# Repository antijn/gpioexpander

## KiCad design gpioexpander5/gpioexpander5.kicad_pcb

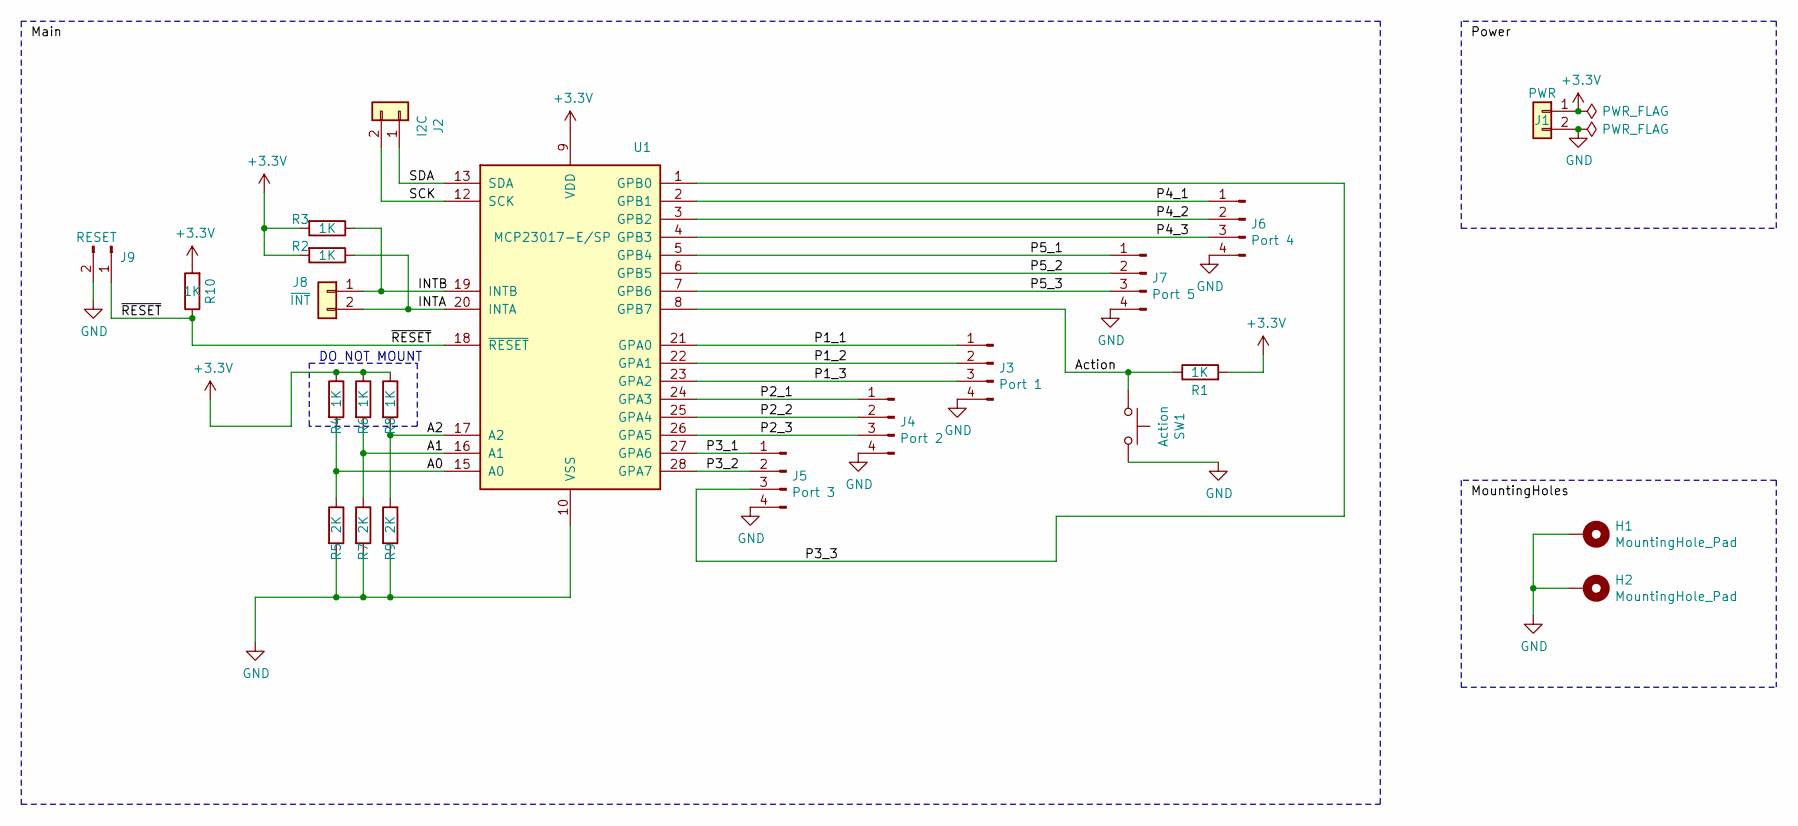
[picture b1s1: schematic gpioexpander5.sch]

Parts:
H1, H2: MountingHole_Pad; MountingHole_3.2mm_M3_Pad
J1: PWR; PinHeader_1x02_P2.54mm_Vertical
J2: I2C; PinHeader_1x02_P2.54mm_Vertical
J3: Port 1; PinHeader_1x04_P2.54mm_Vertical
J4: Port 2; PinHeader_1x04_P2.54mm_Vertical
J5: Port 3; PinHeader_1x04_P2.54mm_Vertical
J6: Port 4; PinHeader_1x04_P2.54mm_Vertical
J7: Port 5; PinHeader_1x04_P2.54mm_Vertical
J8: ~INT; PinHeader_1x02_P2.54mm_Vertical
J9: RESET; PinHeader_1x02_P2.54mm_Vertical
R1, R2, R3, R4, R6, R8, R10: 1K; R_0805_2012Metric_Pad1.15x1.40mm_HandSolder
R5, R7, R9: 2K; R_0805_2012Metric_Pad1.15x1.40mm_HandSolder
SW1: Action; SW_PUSH_6mm
U1: MCP23017-E/SP; SOIC-28W_7.5x17.9mm_P1.27mm

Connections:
+3V3: J1.1, R1.2, R2.2, R3.2, R4.1, R6.1, R8.1, R10.2, U1.9 (VDD)
/A0: R4.2, R5.1, U1.15 (A0)
/A1: R6.2, R7.1, U1.16 (A1)
/A2: R8.2, R9.1, U1.17 (A2)
/Action: R1.1, SW1.1, U1.8 (GPB7)
/INTA: J8.2, R2.1, U1.20 (INTA)
/INTB: J8.1, R3.1, U1.19 (INTB)
/P1_1: J3.1, U1.21 (GPA0)
/P1_2: J3.2, U1.22 (GPA1)
/P1_3: J3.3, U1.23 (GPA2)
/P2_1: J4.1, U1.24 (GPA3)
/P2_2: J4.2, U1.25 (GPA4)
/P2_3: J4.3, U1.26 (GPA5)
/P3_1: J5.1, U1.27 (GPA6)
/P3_2: J5.2, U1.28 (GPA7)
/P3_3: J5.3, U1.1 (GPB0)
/P4_1: J6.1, U1.2 (GPB1)
/P4_2: J6.2, U1.3 (GPB2)
/P4_3: J6.3, U1.4 (GPB3)
/P5_1: J7.1, U1.5 (GPB4)
/P5_2: J7.2, U1.6 (GPB5)
/P5_3: J7.3, U1.7 (GPB6)
/SCK: J2.2, U1.12 (SCK)
/SDA: J2.1, U1.13 (SDA)
/~RESET: J9.1, R10.1, U1.18 (~RESET~)
GND: H1.1, H2.1, J1.2, J3.4, J4.4, J5.4, J6.4, J7.4, J9.2, R5.2, R7.2, R9.2, SW1.2, U1.10 (VSS)

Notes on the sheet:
DO NOT MOUNT

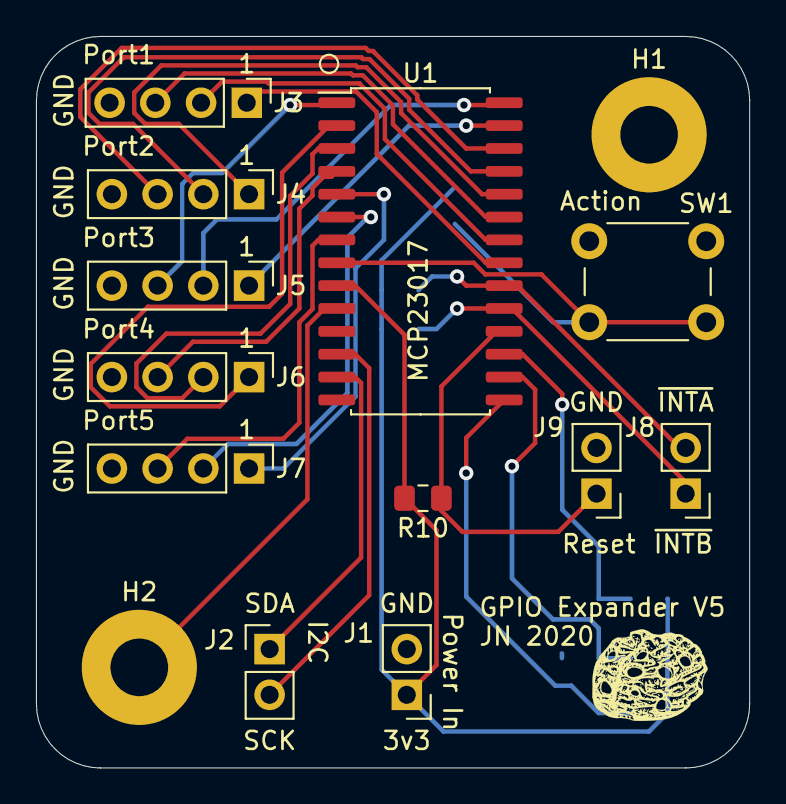
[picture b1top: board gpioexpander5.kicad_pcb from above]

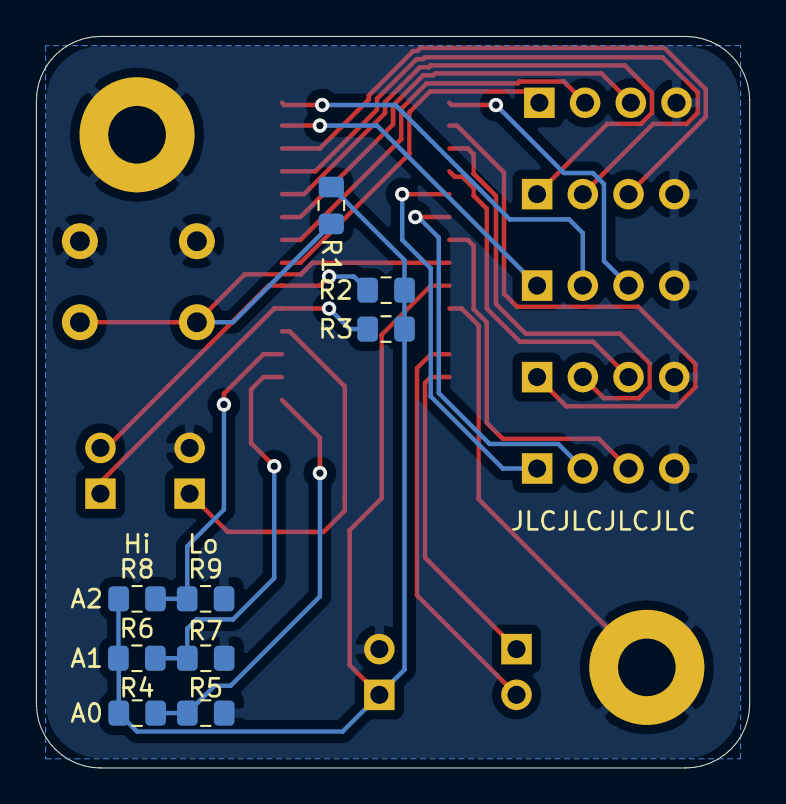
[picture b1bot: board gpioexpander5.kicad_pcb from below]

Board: 2 copper layers, 39.6 x 40.6 mm, 23 parts (9 on the bottom side), 26 nets.

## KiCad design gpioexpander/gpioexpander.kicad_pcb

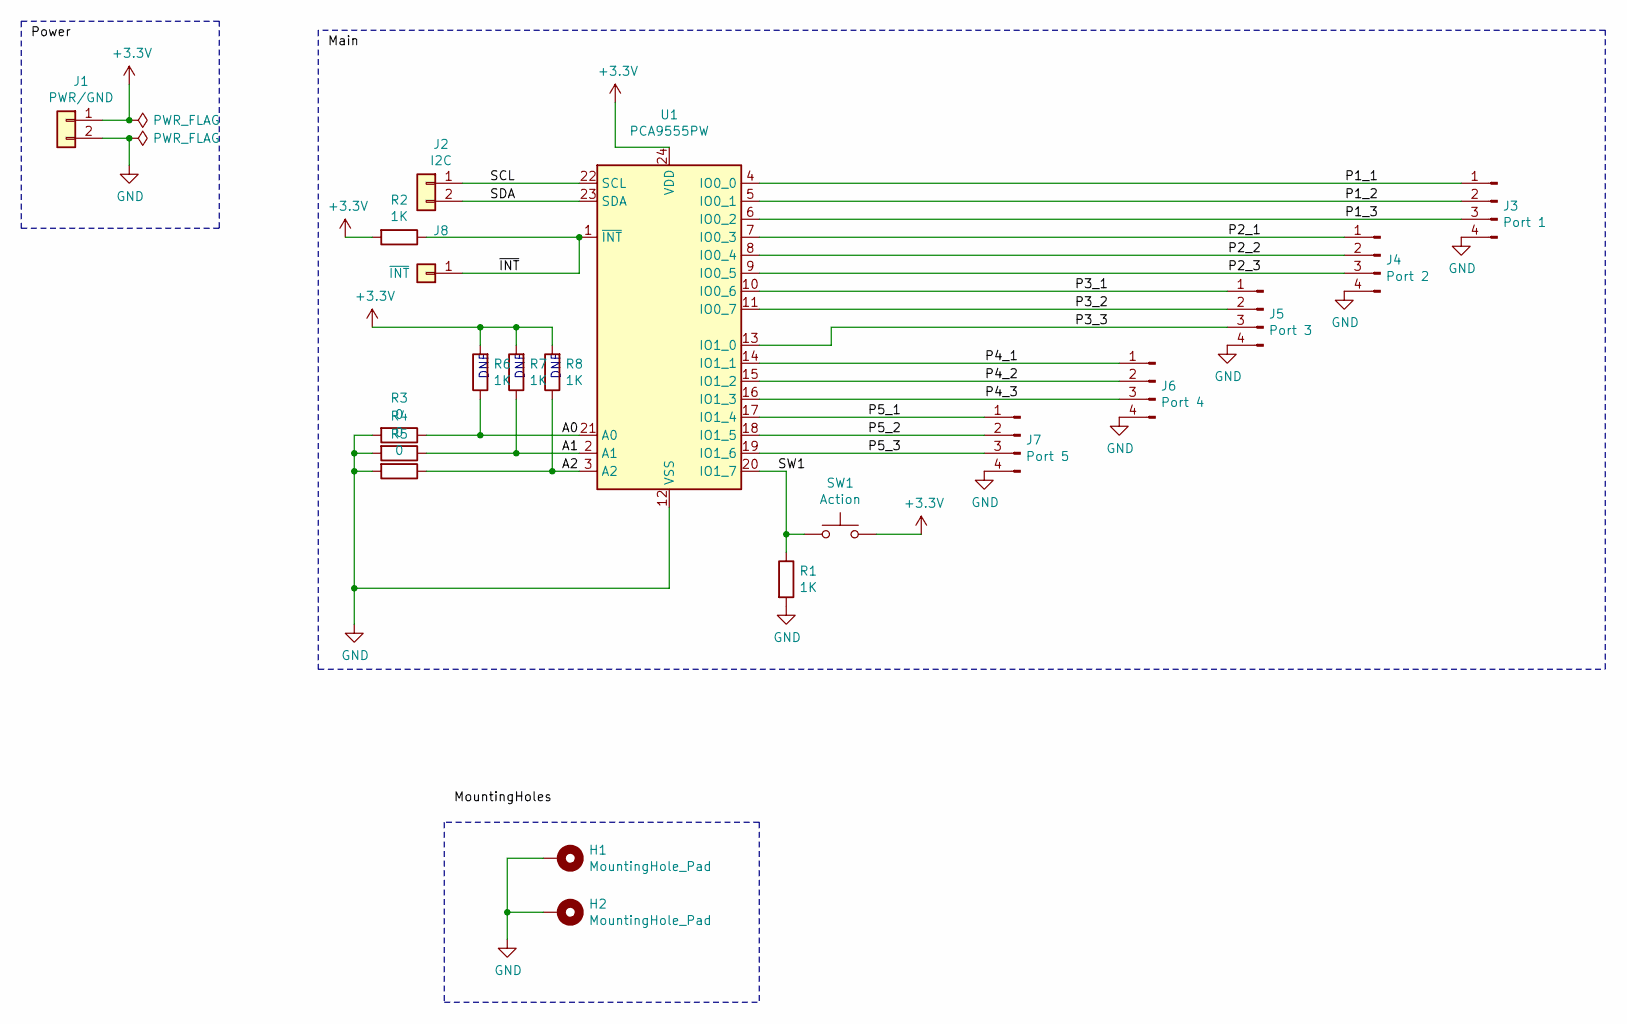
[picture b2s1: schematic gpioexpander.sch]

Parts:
H1, H2: MountingHole_Pad; MountingHole_3.2mm_M3_Pad
J1: PWR/GND; PinHeader_1x02_P2.54mm_Vertical
J2: I2C; PinHeader_1x02_P2.54mm_Vertical
J3: Port 1; PinHeader_1x04_P2.54mm_Vertical
J4: Port 2; PinHeader_1x04_P2.54mm_Vertical
J5: Port 3; PinHeader_1x04_P2.54mm_Vertical
J6: Port 4; PinHeader_1x04_P2.54mm_Vertical
J7: Port 5; PinHeader_1x04_P2.54mm_Vertical
J8: ~INT; PinHeader_1x01_P2.54mm_Vertical
R1: 1K; R_0603_1608Metric_Pad1.05x0.95mm_HandSolder; LCSC C21190
R2: 1K; R_0603_1608Metric_Pad1.05x0.95mm_HandSolder
R3, R4, R5: 0; R_0805_2012Metric_Pad1.15x1.40mm_HandSolder
R6, R7, R8: 1K; R_0805_2012Metric_Pad1.15x1.40mm_HandSolder
SW1: Action; SW_PUSH_6mm
U1: PCA9555PW; TSSOP-24_4.4x7.8mm_P0.65mm; LCSC C128392

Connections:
+3V3: J1.1, R2.2, R6.2, R7.2, R8.2, SW1.2, U1.24 (VDD)
/A0: R3.1, R6.1, U1.21 (A0)
/A1: R4.1, R7.1, U1.2 (A1)
/A2: R5.1, R8.1, U1.3 (A2)
/P1_1: J3.1, U1.4 (IO0_0)
/P1_2: J3.2, U1.5 (IO0_1)
/P1_3: J3.3, U1.6 (IO0_2)
/P2_1: J4.1, U1.7 (IO0_3)
/P2_2: J4.2, U1.8 (IO0_4)
/P2_3: J4.3, U1.9 (IO0_5)
/P3_1: J5.1, U1.10 (IO0_6)
/P3_2: J5.2, U1.11 (IO0_7)
/P3_3: J5.3, U1.13 (IO1_0)
/P4_1: J6.1, U1.14 (IO1_1)
/P4_2: J6.2, U1.15 (IO1_2)
/P4_3: J6.3, U1.16 (IO1_3)
/P5_1: J7.1, U1.17 (IO1_4)
/P5_2: J7.2, U1.18 (IO1_5)
/P5_3: J7.3, U1.19 (IO1_6)
/SCL: J2.1, U1.22 (SCL)
/SDA: J2.2, U1.23 (SDA)
/SW1: R1.1, SW1.1, U1.20 (IO1_7)
/~INT: J8.1, R2.1, U1.1 (~INT)
GND: H1.1, H2.1, J1.2, J3.4, J4.4, J5.4, J6.4, J7.4, R1.2, R3.2, R4.2, R5.2, U1.12 (VSS)

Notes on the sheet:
DNF

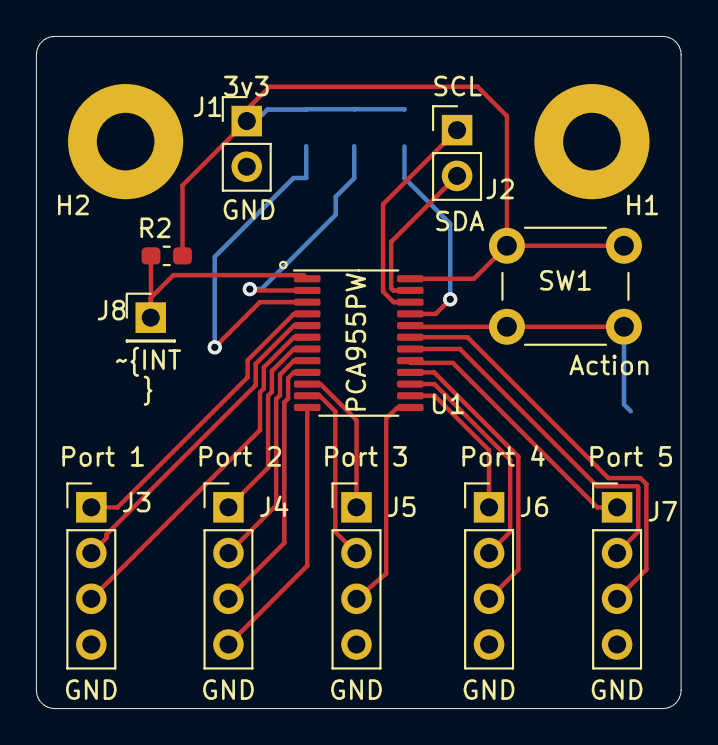
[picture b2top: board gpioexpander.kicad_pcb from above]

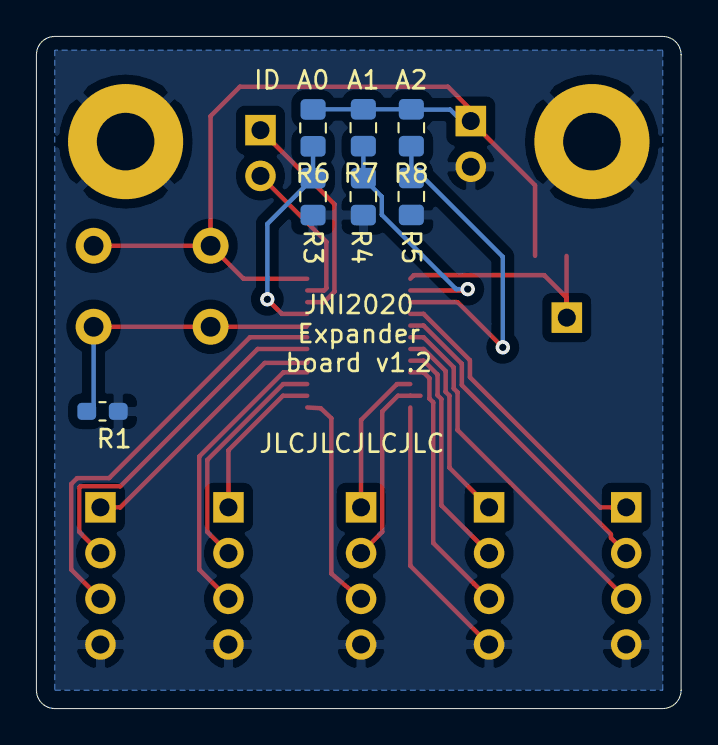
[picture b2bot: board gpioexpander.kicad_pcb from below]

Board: 2 copper layers, 35.8 x 37.3 mm, 20 parts (7 on the bottom side), 24 nets.

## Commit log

2020-09-05 Mark1
2020-09-05 V4 - autorouted and reworked
2020-09-17 Production run 1
2020-10-18 Add hi/lo ot addr
2020-10-18 gpioexpander v5.1
    4 pin headers document hi/lo side
2023-11-24 gpioexpander v6
